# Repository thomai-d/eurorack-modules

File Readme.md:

# What is this?

Collection of eurorack modules I designed.

You can find documentation, as well as schematics and gerber files.

All modules are licenced under **CC BY-SA 4.0**.

# CV-Switch

Module that outputs **two switched control voltages** with **exponential RC slew limiters**.

[More info & demo video](cv-switch/)

# Summix

3-channel summing mixer with 4 inputs and 2 buffered outputs for each channel.

[More info](summix/)

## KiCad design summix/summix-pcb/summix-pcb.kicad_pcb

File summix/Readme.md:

# Summix

A simple, low-cost Eurorack 3-channel summing mixer with 4 inputs and 2 separately buffered outputs for each channel.

The mixer is fully **DC-coupled**, **Unit-Gain**, **Non-Inverting**. Nothing fancy. Just adding signals.

## Repository content

- doc/BOM.csv: Bill of materials

- summix-pcb/
    - summix-pcb.kicad_sch / summix-pcb.kicad_pcb: main circuit board
    - gerbers/: generated gerbers/drills for the main board

- summix-panel/
    - summix-panel.kicad_pcb: front panel PCB (text/art + mounting)
    - gerbers/: generated gerbers/drills for the panel

# How it works

## Block diagram

```mermaid
%%{init: {"themeVariables": {"fontSize": "12px"}, "flowchart": {"nodeSpacing": 25, "rankSpacing": 25}}}%%
flowchart LR

    IN1["Input 1"] --> SUM["Inverting summing amp"]
    IN2["Input 2"] --> SUM
    IN3["Input 3"] --> SUM
    IN3["Input 4"] --> SUM

    SUM --> INV["Inverter"]
    INV --> BUF1["Output buffer 1"] --> OUT1["Output 1"]
    INV --> BUF2["Output buffer 2"] --> OUT2["Output 2"]
```

## Schematic

The schematic of a single channel (there are 3 of them):

## License

Licensed under **CC BY-SA 4.0**.

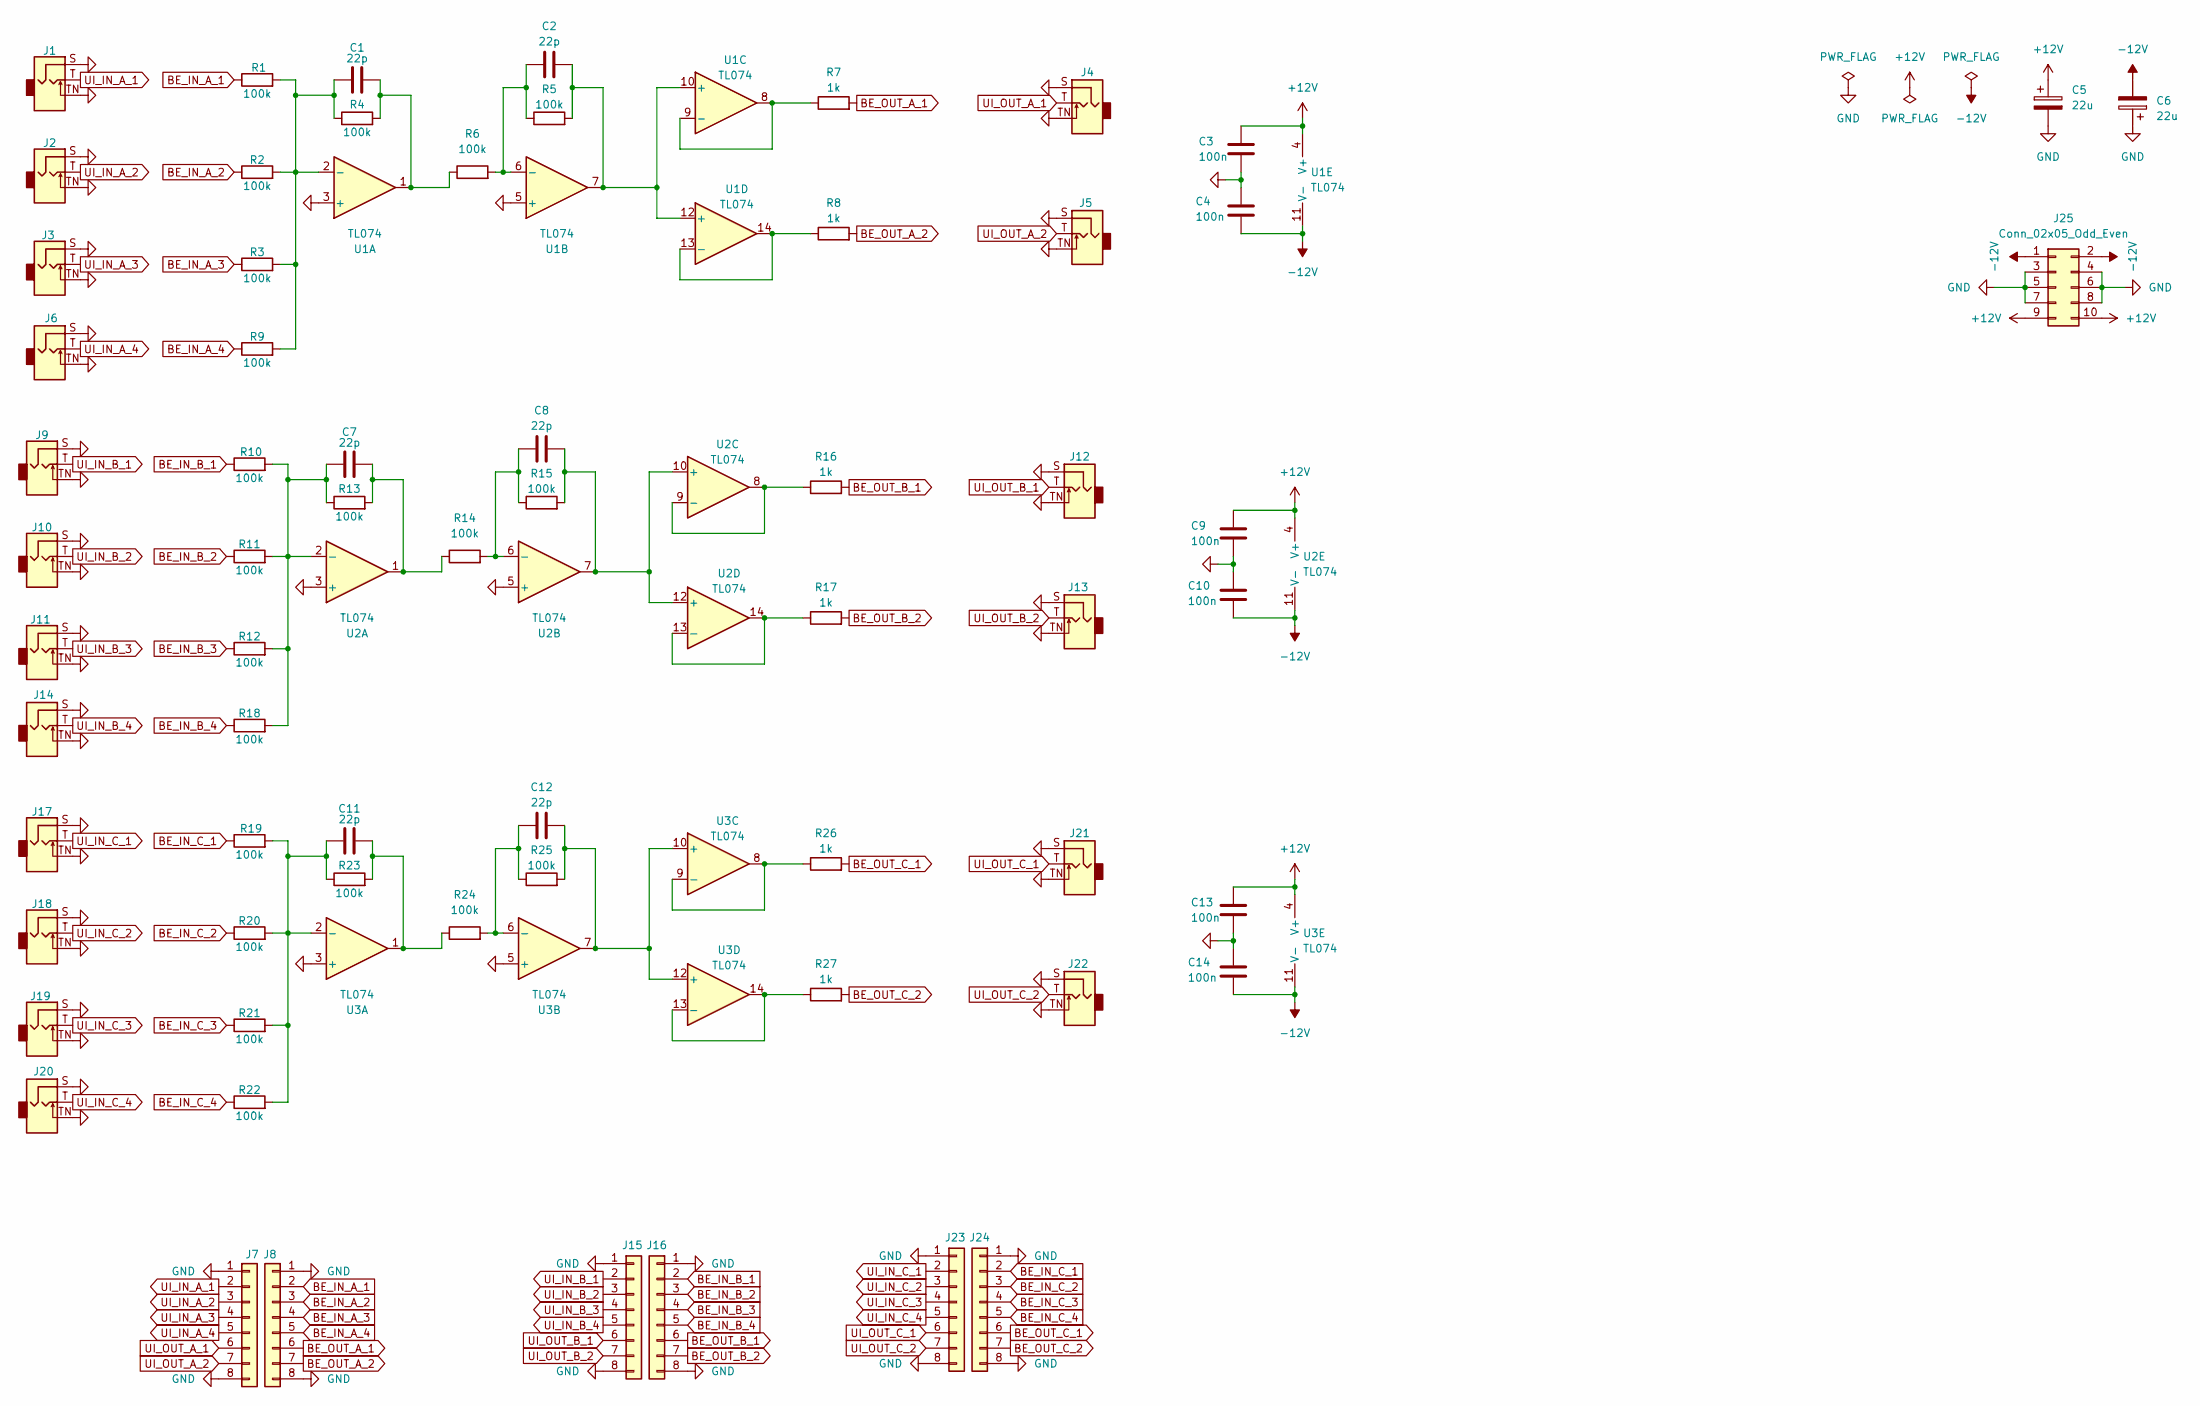
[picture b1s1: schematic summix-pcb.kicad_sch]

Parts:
C1, C2, C7, C8, C11, C12: 22p; C_0805_2012Metric_Pad1.18x1.45mm_HandSolder
C3, C4, C9, C10, C13, C14: 100n; C_0805_2012Metric_Pad1.18x1.45mm_HandSolder
C5, C6: 22u; CP_Elec_6.3x5.8
J1, J2, J3, J4, J5, J6, J9, J10, J11, J12, J13, J14, J17, J18, J19, J20, J21, J22: AudioJack2_SwitchT; Thonk_mono
J7, J8, J15, J16, J23, J24: Conn_01x08; PinHeader_1x08_P2.54mm_Vertical
J25: Conn_02x05_Odd_Even; IDC-Header_2x05_P2.54mm_Vertical
R1, R2, R3, R4, R5, R6, R9, R10, R11, R12, R13, R14, R15, R18, R19, R20, R21, R22, R23, R24, R25: 100k; R_0805_2012Metric_Pad1.20x1.40mm_HandSolder
R7, R8, R16, R17, R26, R27: 1k; R_0805_2012Metric_Pad1.20x1.40mm_HandSolder
U1, U2, U3: TL074; SOIC-14_3.9x8.7mm_P1.27mm

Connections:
+12V: C3.1, C5.1, C9.1, C13.1, J25.9, J25.10, U1.4 (V+), U2.4 (V+), U3.4 (V+)
-12V: C4.2, C6.2, C10.2, C14.2, J25.1, J25.2, U1.11 (V-), U2.11 (V-), U3.11 (V-)
BE_IN_A_1: J8.2, R1.1
BE_IN_A_2: J8.3, R2.1
BE_IN_A_3: J8.4, R3.1
BE_IN_A_4: J8.5, R9.1
BE_IN_B_1: J16.2, R10.1
BE_IN_B_2: J16.3, R11.1
BE_IN_B_3: J16.4, R12.1
BE_IN_B_4: J16.5, R18.1
BE_IN_C_1: J24.2, R19.1
BE_IN_C_2: J24.3, R20.1
BE_IN_C_3: J24.4, R21.1
BE_IN_C_4: J24.5, R22.1
BE_OUT_A_1: J8.6, R7.2
BE_OUT_A_2: J8.7, R8.2
BE_OUT_B_1: J16.6, R16.2
BE_OUT_B_2: J16.7, R17.2
BE_OUT_C_1: J24.6, R26.2
BE_OUT_C_2: J24.7, R27.2
GND: C3.2, C4.1, C5.2, C6.1, C9.2, C10.1, C13.2, C14.1, J1.S, J1.TN, J2.S, J2.TN, J3.S, J3.TN, J4.S, J4.TN, J5.S, J5.TN, J6.S, J6.TN, J7.1, J7.8, J8.1, J8.8, J9.S, J9.TN, J10.S, J10.TN, J11.S, J11.TN, J12.S, J12.TN, J13.S, J13.TN, J14.S, J14.TN, J15.1, J15.8, J16.1, J16.8, J17.S, J17.TN, J18.S, J18.TN, J19.S, J19.TN, J20.S, J20.TN, J21.S, J21.TN, J22.S, J22.TN, J23.1, J23.8, J24.1, J24.8, J25.3, J25.4, J25.5, J25.6, J25.7, J25.8, U1.3 (+), U1.5 (+), U2.3 (+), U2.5 (+), U3.3 (+), U3.5 (+)
unnamed: C1.2, R4.2, R6.1, U1.1
unnamed: C7.2, R13.2, R14.1, U2.1
unnamed: C11.2, R23.2, R24.1, U3.1
unnamed: C1.1, R1.2, R2.2, R3.2, R4.1, R9.2, U1.2 (-)
unnamed: C2.1, R5.1, R6.2, U1.6 (-)
unnamed: C2.2, R5.2, U1.7, U1.10 (+), U1.12 (+)
unnamed: R7.1, U1.8, U1.9 (-)
unnamed: R8.1, U1.13 (-), U1.14
unnamed: C7.1, R10.2, R11.2, R12.2, R13.1, R18.2, U2.2 (-)
unnamed: C8.1, R14.2, R15.1, U2.6 (-)
unnamed: C8.2, R15.2, U2.7, U2.10 (+), U2.12 (+)
unnamed: R16.1, U2.8, U2.9 (-)
unnamed: R17.1, U2.13 (-), U2.14
unnamed: C11.1, R19.2, R20.2, R21.2, R22.2, R23.1, U3.2 (-)
unnamed: C12.1, R24.2, R25.1, U3.6 (-)
unnamed: C12.2, R25.2, U3.7, U3.10 (+), U3.12 (+)
unnamed: R26.1, U3.8, U3.9 (-)
unnamed: R27.1, U3.13 (-), U3.14
UI_IN_A_1: J1.T, J7.2
UI_IN_A_2: J2.T, J7.3
UI_IN_A_3: J3.T, J7.4
UI_IN_A_4: J6.T, J7.5
UI_IN_B_1: J9.T, J15.2
UI_IN_B_2: J10.T, J15.3
UI_IN_B_3: J11.T, J15.4
UI_IN_B_4: J14.T, J15.5
UI_IN_C_1: J17.T, J23.2
UI_IN_C_2: J18.T, J23.3
UI_IN_C_3: J19.T, J23.4
UI_IN_C_4: J20.T, J23.5
UI_OUT_A_1: J4.T, J7.6
UI_OUT_A_2: J5.T, J7.7
UI_OUT_B_1: J12.T, J15.6
UI_OUT_B_2: J13.T, J15.7
UI_OUT_C_1: J21.T, J23.6
UI_OUT_C_2: J22.T, J23.7

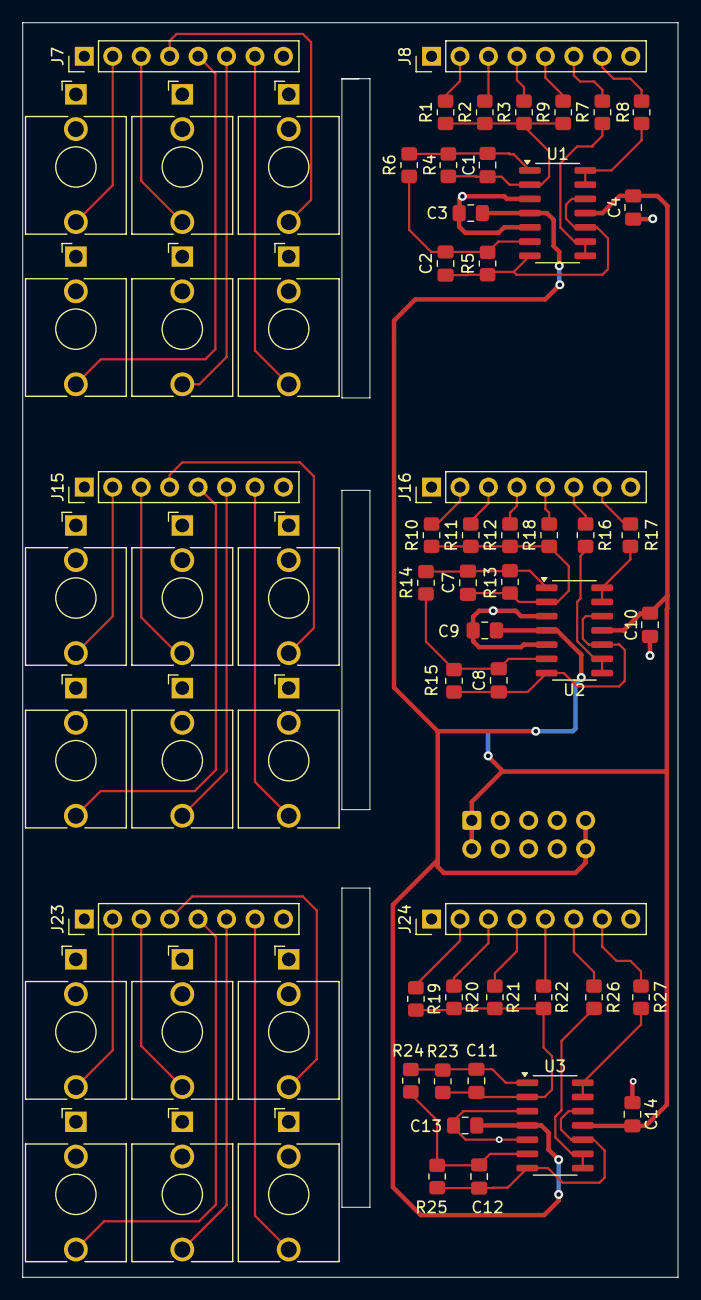
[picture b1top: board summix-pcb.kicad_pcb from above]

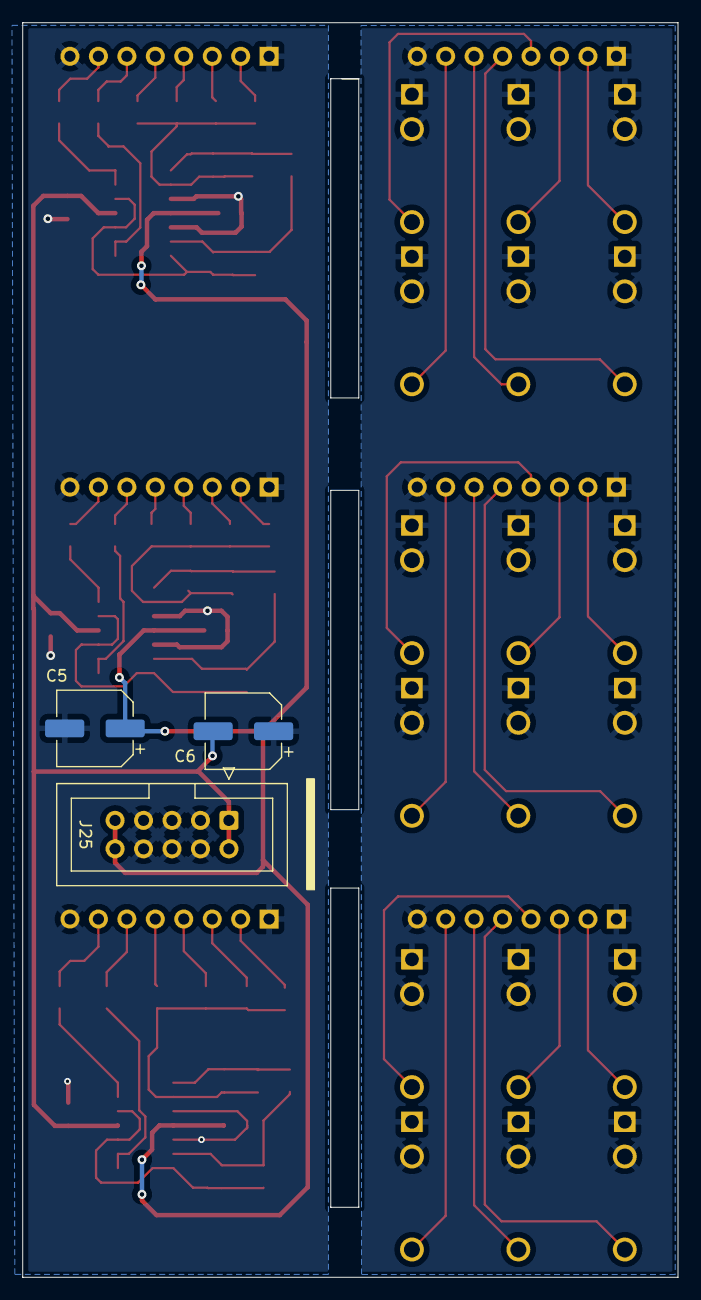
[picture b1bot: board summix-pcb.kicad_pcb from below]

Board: 2 copper layers, 58.5 x 112.0 mm, 69 parts (3 on the bottom side), 57 nets.

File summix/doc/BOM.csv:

Reference,Qty,Value,Reichelt Part,Footprint
"C1,C2,C7,C8,C11,C12",6,22p,NPO-G0805 22P,Capacitor_SMD:C_0805_2012Metric_Pad1.18x1.45mm_HandSolder
"C3,C4,C9,C10,C13,C14",6,100n,X7R-G0805 100N,Capacitor_SMD:C_0805_2012Metric_Pad1.18x1.45mm_HandSolder
"C5,C6",2,22u,SMD ELKO 22/35,Capacitor_SMD:CP_Elec_6.3x5.8
"J1,J2,J3,J4,J5,J6,J9,J10,J11,J12,J13,J14,J17,J18,J19,J20,J21,J22",18,AudioJack2_SwitchT,,MyParts:Thonk_mono
"J7,J8,J15,J16,J23,J24",6,Conn_01x08,,Connector_PinHeader_2.54mm:PinHeader_1x08_P2.54mm_Vertical
J25,1,Conn_02x05_Odd_Even,,Connector_IDC:IDC-Header_2x05_P2.54mm_Vertical
"R1,R2,R3,R4,R5,R6,R9,R10,R11,R12,R13,R14,R15,R18,R19,R20,R21,R22,R23,R24,R25",21,100k,SMD-0805 100K,Resistor_SMD:R_0805_2012Metric_Pad1.20x1.40mm_HandSolder
"R7,R8,R16,R17,R26,R27",6,1k,"SMD-0805 1,00K",Resistor_SMD:R_0805_2012Metric_Pad1.20x1.40mm_HandSolder
"U1,U2,U3",3,TL074,TL 074 CD SMD,Package_SO:SOIC-14_3.9x8.7mm_P1.27mm

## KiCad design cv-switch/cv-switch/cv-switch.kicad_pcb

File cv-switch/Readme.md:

# CV-Switch

A simple, low-cost Eurorack DIY module that outputs **two switched control voltages** with **exponential RC slew limiters**, focused on simple schematics.

Each output can be set to one of **two knob-defined voltages**. A single **DPDT toggle switch** flips _both outputs_ at the same time. Each output also has a **slew** control with an **exponential RC** curve - if you modulate pitch CV, you can "hear" the capacitor charge. I love it :-)

## Demo-Video

Left module controls pitch and twist of 4ms Ensemble. Right module controls VCF highpass cutoff frequency.

https://github.com/user-attachments/assets/a2533407-694b-4e1d-8e46-d9b85c6f17b2

## Repository content

- doc/BOM.csv: Bill of materials

- cv-switch/
  - cv-switch.kicad_sch / cv-switch.kicad_pcb: main circuit board
  - Output/: generated gerbers/drills for the main board

- cv-switch-panel/
  - cv-switch-panel.kicad_pcb: front panel PCB (text/art + mounting)
  - Output/: generated gerbers/drills for the panel

# How it works

## Block diagram

```mermaid
%%{init: {"themeVariables": {"fontSize": "12px"}, "flowchart": {"nodeSpacing": 25, "rankSpacing": 25}}}%%
flowchart LR

  subgraph "Channel 2"
    A2["Preset A knob"] --> S2{"A/B select"}
    B2["Preset B knob"] --> S2
    S2 --> SL2["Slew RC"] --> BUF2["Buffer op amp"] --> OUT2["Output 2 jack"]
  end

  subgraph "Channel 1"
    A1["Preset A knob"] --> S1{"A/B select"}
    B1["Preset B knob"] --> S1
    S1 --> SL1["Slew RC"] --> BUF1["Buffer op amp"] --> OUT1["Output 1 jack"]
  end

  SW["DPDT toggle switch"] -. "switches both" .-> S1
  SW -. "switches both" .-> S2
```

## Schematic

The schematic of a single channel (there are 2 of them):

]

## License

Licensed under **CC BY-SA 4.0**.

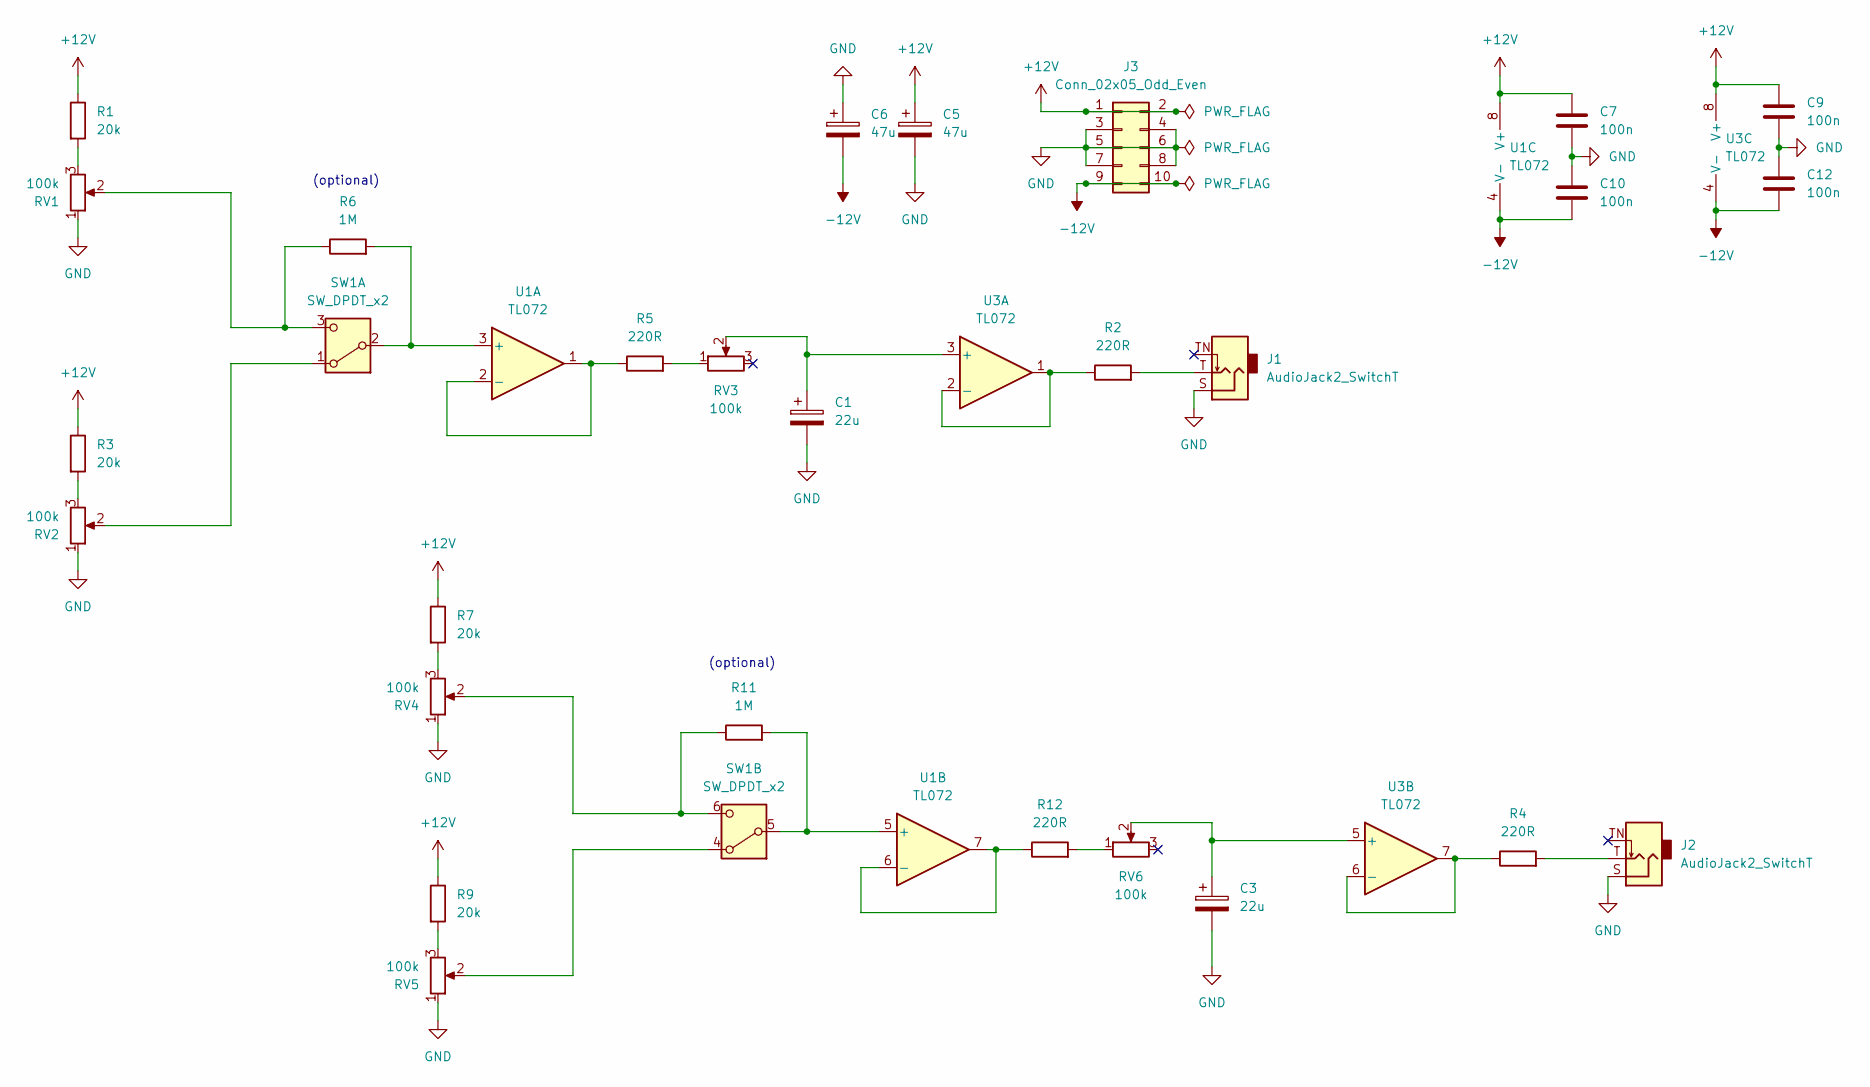
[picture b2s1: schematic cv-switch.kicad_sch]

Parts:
C1, C3: 22u; CP_Radial_D5.0mm_P2.50mm
C5, C6: 47u; CP_Radial_D5.0mm_P2.50mm
C7, C9, C10, C12: 100n; C_Disc_D6.0mm_W2.5mm_P5.00mm
J1, J2: AudioJack2_SwitchT; Jack_3.5mm_QingPu_WQP-PJ398SM_Vertical_CircularHoles
J3: Conn_02x05_Odd_Even; PinHeader_2x05_P2.54mm_Vertical
R1, R3, R7, R9: 20k; R_Axial_DIN0207_L6.3mm_D2.5mm_P7.62mm_Horizontal
R2, R4, R5, R12: 220R; R_Axial_DIN0207_L6.3mm_D2.5mm_P7.62mm_Horizontal
R6, R11: 1M; R_Axial_DIN0207_L6.3mm_D2.5mm_P7.62mm_Horizontal
RV1, RV2, RV3, RV4, RV5, RV6: 100k; Potentiometer_Alpha_RD901F-40-00D_Single_Vertical
SW1: SW_DPDT_x2; MS 500F
U1, U3: TL072; DIP-8_W7.62mm_LongPads

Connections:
+12V: C5.1, C7.1, C9.1, J3.1, J3.2, R1.1, R3.1, R7.1, R9.1, U1.8 (V+), U3.8 (V+)
-12V: C6.2, C10.2, C12.2, J3.9, J3.10, U1.4 (V-), U3.4 (V-)
GND: C1.2, C3.2, C5.2, C6.1, C7.2, C9.2, C10.1, C12.1, J1.S, J2.S, J3.3, J3.4, J3.5, J3.6, J3.7, J3.8, RV1.1, RV2.1, RV4.1, RV5.1
unnamed: J1.T, R2.2
unnamed: J2.T, R4.2
unnamed: R1.2, RV1.3
unnamed: R3.2, RV2.3
unnamed: R5.2, RV3.1
unnamed: R7.2, RV4.3
unnamed: R9.2, RV5.3
unnamed: R12.2, RV6.1
unnamed: RV2.2, SW1.1 (A)
unnamed: R6.2, SW1.2 (B), U1.3 (+)
unnamed: R6.1, RV1.2, SW1.3 (C)
unnamed: RV5.2, SW1.4 (A)
unnamed: R11.2, SW1.5 (B), U1.5 (+)
unnamed: R11.1, RV4.2, SW1.6 (C)
unnamed: R5.1, U1.1, U1.2 (-)
unnamed: R12.1, U1.6 (-), U1.7
unnamed: C1.1, RV3.2, U3.3 (+)
unnamed: R2.1, U3.1, U3.2 (-)
unnamed: C3.1, RV6.2, U3.5 (+)
unnamed: R4.1, U3.6 (-), U3.7

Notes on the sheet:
(optional)

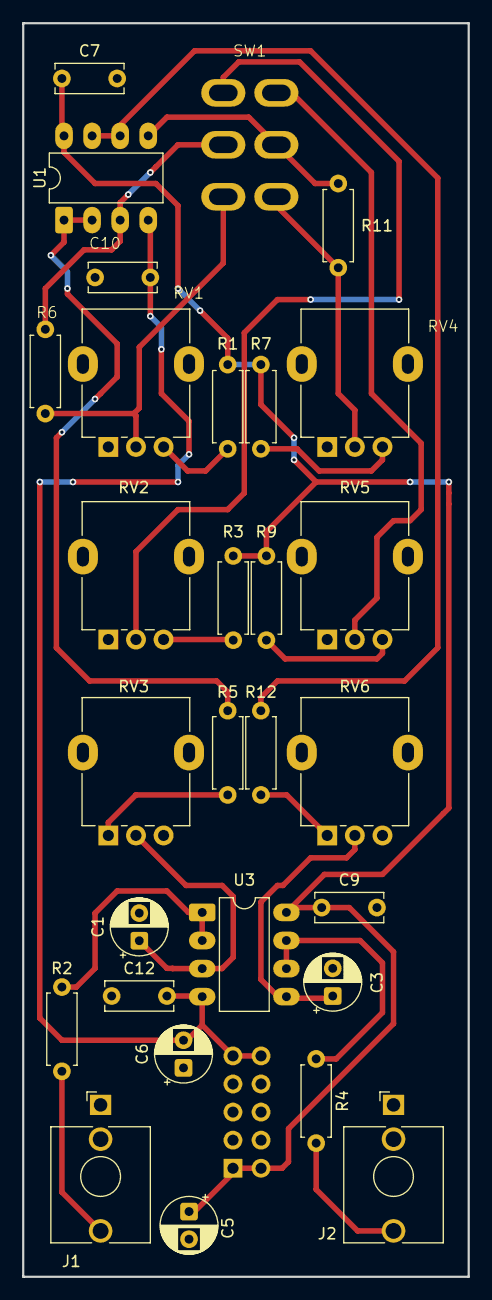
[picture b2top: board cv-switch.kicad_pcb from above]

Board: 2 copper layers, 40.3 x 113.4 mm, 30 parts (1 on the bottom side), 23 nets.

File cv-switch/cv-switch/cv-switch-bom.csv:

"Reference","Qty","Value","DNP","Exclude from BOM","Exclude from Board","Footprint","Datasheet"
"C1,C3","2","22u","","","","Capacitor_THT:CP_Radial_D5.0mm_P2.50mm","~"
"C5,C6","2","47u","","","","Capacitor_THT:CP_Radial_D5.0mm_P2.50mm","~"
"C7,C9,C10,C12","4","100n","","","","Capacitor_THT:C_Disc_D6.0mm_W2.5mm_P5.00mm","~"
"J1,J2","2","AudioJack2_SwitchT","","","","Connector_Audio:Jack_3.5mm_QingPu_WQP-PJ398SM_Vertical_CircularHoles","~"
"J3","1","Conn_02x05_Odd_Even","","","","Connector_PinHeader_2.54mm:PinHeader_2x05_P2.54mm_Vertical","~"
"R1,R3,R7,R9","4","20k","","","","Resistor_THT:R_Axial_DIN0207_L6.3mm_D2.5mm_P7.62mm_Horizontal","~"
"R2,R4,R5,R12","4","220R","","","","Resistor_THT:R_Axial_DIN0207_L6.3mm_D2.5mm_P7.62mm_Horizontal","~"
"R6,R11","2","1M","","","","Resistor_THT:R_Axial_DIN0207_L6.3mm_D2.5mm_P7.62mm_Horizontal","~"
"RV1,RV2,RV3,RV4,RV5,RV6","6","100k","","","","Potentiometer_THT:Potentiometer_Alpha_RD901F-40-00D_Single_Vertical","~"
"SW1","1","SW_DPDT_x2","","","","Reichelt:MS 500F","~"
"U1,U3","2","TL072","","","","Package_DIP:DIP-8_W7.62mm_LongPads","http://www.ti.com/lit/ds/symlink/tl071.pdf"

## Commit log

2026-03-08 Add project readme
2026-03-08 Add cv-switch module
2026-03-13 Small fixes for cv-switch
2026-03-18 Add summix module
2026-03-29 Update cv-switch docs
